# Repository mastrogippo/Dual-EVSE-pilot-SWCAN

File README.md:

## EVSE pilot circuit test

[Writeup and pics here](http://www.mastrogippo.it/2019/08/first-prototype-and-test-hardware/)

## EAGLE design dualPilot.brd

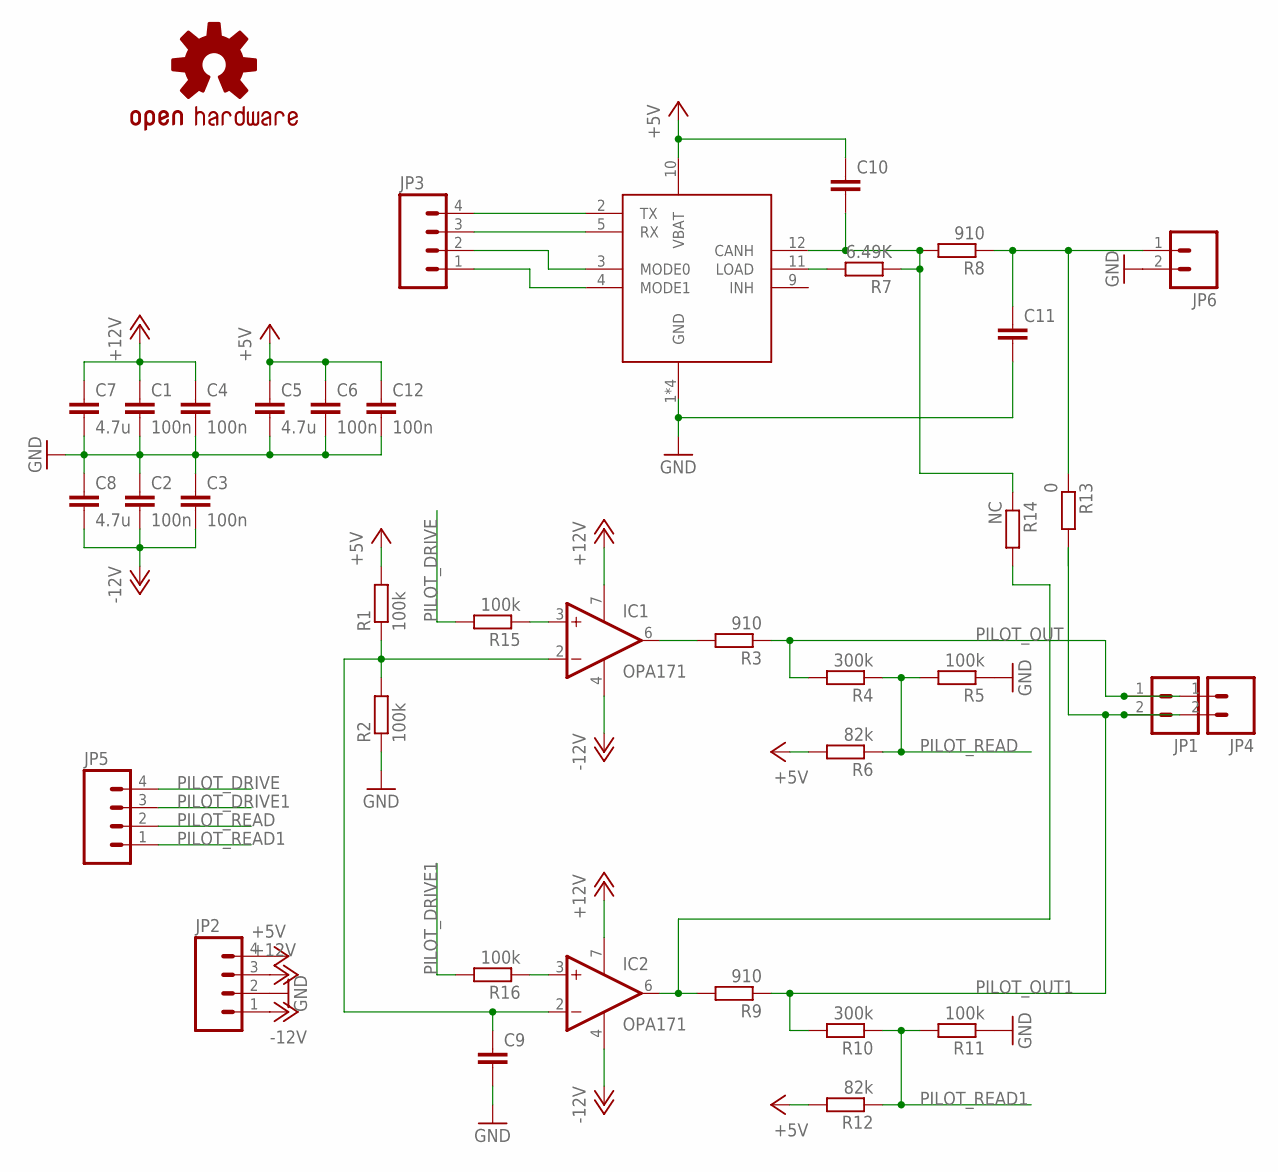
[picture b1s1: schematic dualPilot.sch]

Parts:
C1, C2, C3, C4, C6, C12: 100n; 0805
C5, C7, C8: 4.7u; 0805
C9, C10, C11: CAP0805; 0805
IC1, IC2: OPA171; SO08
JP1, JP6: M02LOCK_LONGPADS; 1X02_LOCK_LONGPADS
JP2, JP3, JP5: M04LONGPADS; 1X04_LONGPADS
JP4: M025MM; SCREWTERMINAL-5MM-2
R1, R2, R5, R11, R15, R16: 100k; R0805
R3, R8, R9: 910; R1206
R4, R10: 300k; R0805
R6, R12: 82k; R0805
R7: 6.49K; R0805
R13: 0; R0805
R14: NC; R0805
U$1: NCV7356; SO14
U$2: OSHW-LOGOS; OSHW-LOGO-S

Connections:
+5V: C5.1, C6.1, C10.1, C12.1, JP2.4, R1.2, R6.2, R12.2, U$1.10 (VBAT)
+12V: C1.1, C4.1, C7.1, IC1.7 (V+), IC2.7 (V+), JP2.3
-12V: C2.2, C3.2, C8.2, IC1.4 (V-), IC2.4 (V-), JP2.1
GND: C1.2, C2.1, C3.1, C4.2, C5.2, C6.2, C7.2, C8.1, C9.2, C11.2, C12.2, JP2.2, JP6.2, R2.1, R5.1, R11.1, U$1.1 (GND), U$1.7 (GND), U$1.8 (GND), U$1.14 (GND)
unnamed: C9.1, IC1.2 (-IN), IC2.2 (-IN), R1.1, R2.2
unnamed: JP3.3, U$1.5 (RX)
unnamed: IC1.6 (OUT), R3.2
unnamed: C11.1, JP6.1, R8.1, R13.1
unnamed: IC2.3 (+IN), R16.1
unnamed: R7.2, U$1.11 (LOAD)
unnamed: JP3.2, U$1.3 (MODE0)
unnamed: C10.2, R7.1, R8.2, R14.1, U$1.12 (CANH)
unnamed: JP3.1, U$1.4 (MODE1)
unnamed: IC2.6 (OUT), R9.2, R14.2
unnamed: IC1.3 (+IN), R15.1
unnamed: JP3.4, U$1.2 (TX)
PILOT_DRIVE: JP5.4, R15.2
PILOT_DRIVE1: JP5.3, R16.2
PILOT_OUT: JP1.1, JP4.1, R3.1, R4.2
PILOT_OUT1: JP1.2, JP4.2, R9.1, R10.2, R13.2
PILOT_READ: JP5.2, R4.1, R5.2, R6.1
PILOT_READ1: JP5.1, R10.1, R11.2, R12.1

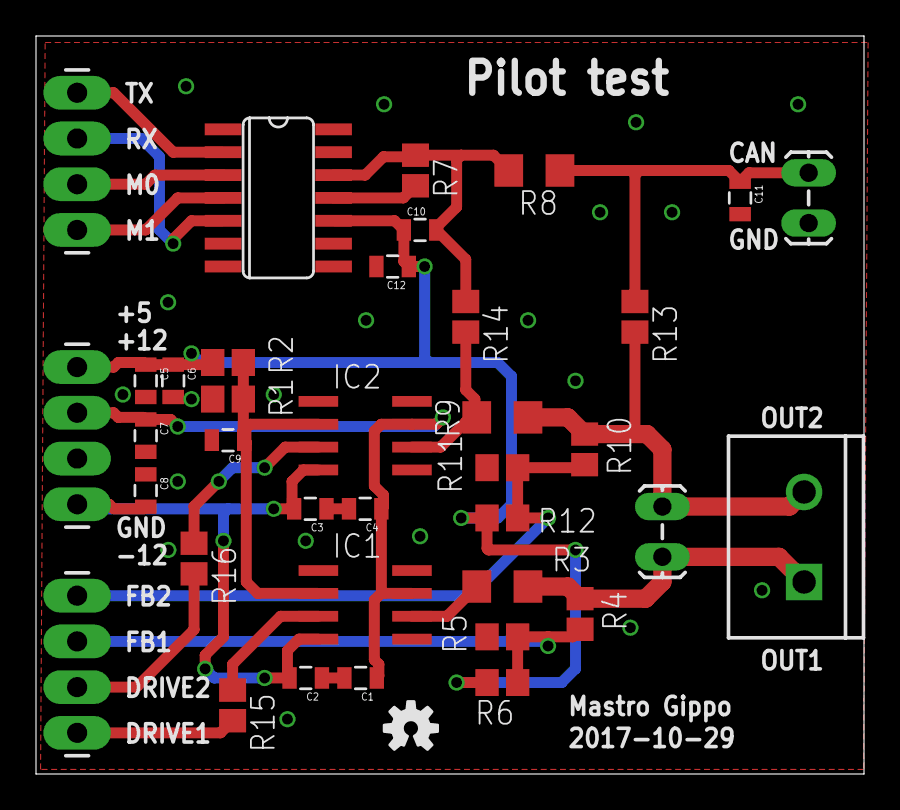
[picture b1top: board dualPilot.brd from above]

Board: 2 copper layers, 46.0 x 41.0 mm, 38 parts (0 on the bottom side), 22 nets.

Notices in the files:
parts and their libraries:
SparkFun-Connectors: Licensing: Creative Commons ShareAlike 4.0 International - https://creativecommons.org/licenses/by-sa/4.0
SparkFun: Licensing: CC v3.0 Share-Alike You are welcome to use this library for commercial purposes.
